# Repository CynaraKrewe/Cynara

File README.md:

A microcontroller and FPGA based, modular prototyping solution covering both hardware and software.

This project was started by Sioux Embedded Systems BV employees in their private time.

The aim of this project is to broaden experience and not only in your own discipline. Members are encouraged to both explore beyond their own discipline(s) and provide guidance to other members were they can. Learning & sharing is what we do. In line of this mindset, everything developed within the project will be made available under terms of a permissive (MIT) license.

Some trivia: 
* [Cynara](https://en.wikipedia.org/wiki/Cynara) is a genus in the sunflower family.
* Addon modules for the Carrier are called Petals.

## Ideas & Goals

#### Target audience

Our target audience is everyone up from the semi-professional hobbyist.

#### Tooling

Goals:
* Keep it simple.
* Keep the complete set of mandatory tooling to a minimum.
* Keep tooling cheap, preferably free.
* Don't reinvent the wheel.

#### Carrier

The Carrier is a complete package of software, HDL, hardware, documentation and partial configuration.

#### Petal

A Petal is a complete package of software, HDL, hardware, documentation and partial configuration.

Goals:
* Keep it simple.
* Keep it cheap.
* Provide a Petal template for jumpstarting.

#### Configuration

Goals:
* Configuration needs to be very intuitive.
* The configuration should understand the restrictions of the microcontroller, FPGA, Carrier and Petal(s).
* A configuration should be validated even before compile-time. Validation during actual designing/writing of the configuration would be nice.

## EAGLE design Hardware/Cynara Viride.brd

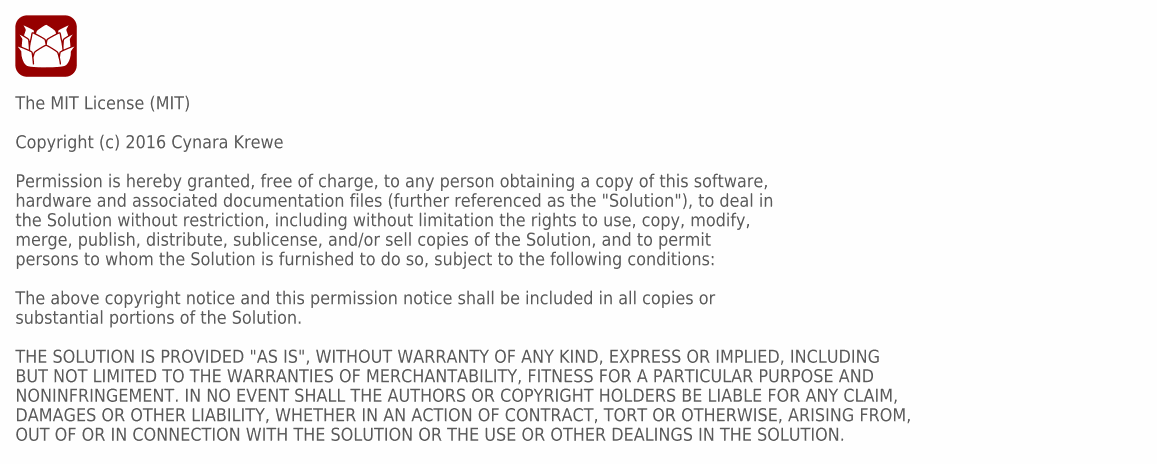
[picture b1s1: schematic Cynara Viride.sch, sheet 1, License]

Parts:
U$21: CYNARA_FRONT; CYNARA_BELOW_W15MM

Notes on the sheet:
The MIT License (MIT) Copyright (c) 2016 Cynara Krewe Permission is hereby granted, free of charge, to any person obtaining a copy of this software, hardware and associated documentation files (further referenced as the "Solution"), to deal in the Solution without restriction, including without lim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

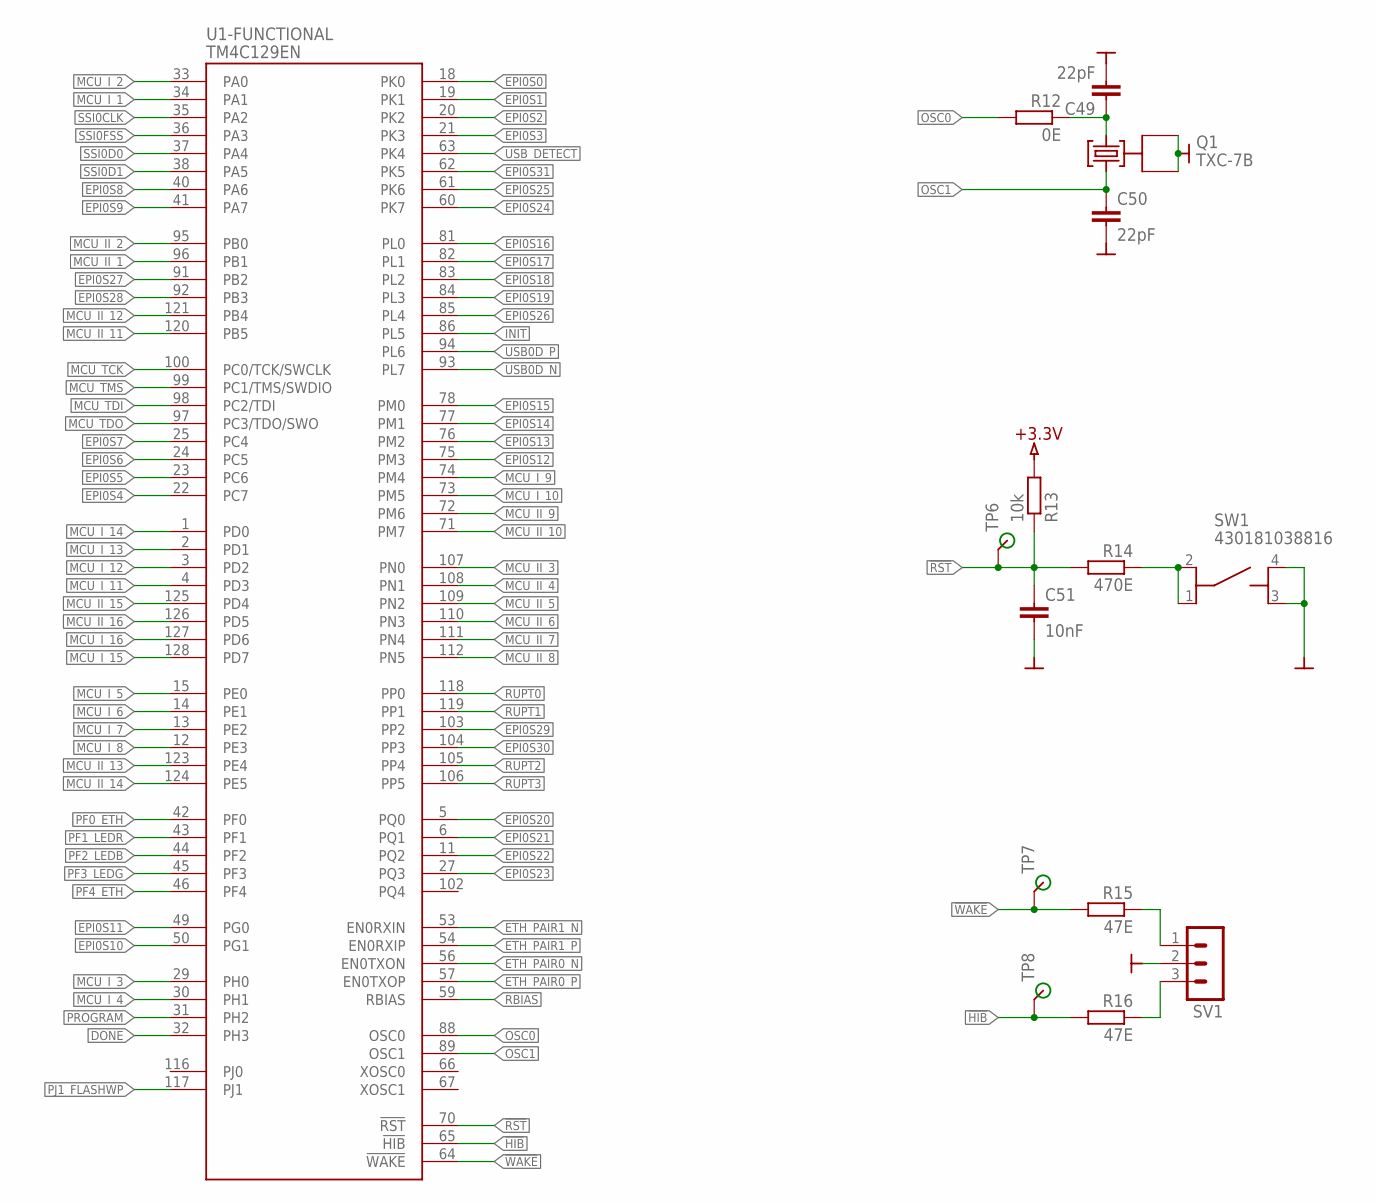
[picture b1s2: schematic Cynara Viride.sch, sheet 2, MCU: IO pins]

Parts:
C49, C50: 22pF; C0603
C51: 10nF; C0603
Q1: TXC-7B
R12: 0E; R0603
R13: 10k; R0603
R14: 470E; R0603
R15, R16: 47E; R0603
SV1: MA03-1
SW1: 430181038816
TP6, TP7, TP8: TP-SMD
U1: TM4C129EN; S-PQFP-G128

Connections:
!HIB: R16.2, TP8.1, U1.65 (!HIB)
!RST: C51.1, R13.1, R14.2, TP6.1, U1.70 (!RST); also elsewhere on the board
!WAKE: R15.2, TP7.1, U1.64 (!WAKE)
+3.3V: R13.2; also elsewhere on the board
DONE: U1.32 (PH3); also elsewhere on the board
EPI0S0: U1.18 (PK0); also elsewhere on the board
EPI0S1: U1.19 (PK1); also elsewhere on the board
EPI0S2: U1.20 (PK2); also elsewhere on the board
EPI0S3: U1.21 (PK3); also elsewhere on the board
EPI0S4: U1.22 (PC7); also elsewhere on the board
EPI0S5: U1.23 (PC6); also elsewhere on the board
EPI0S6: U1.24 (PC5); also elsewhere on the board
EPI0S7: U1.25 (PC4); also elsewhere on the board
EPI0S8: U1.40 (PA6); also elsewhere on the board
EPI0S9: U1.41 (PA7); also elsewhere on the board
EPI0S10: U1.50 (PG1); also elsewhere on the board
EPI0S11: U1.49 (PG0); also elsewhere on the board
EPI0S12: U1.75 (PM3); also elsewhere on the board
EPI0S13: U1.76 (PM2); also elsewhere on the board
EPI0S14: U1.77 (PM1); also elsewhere on the board
EPI0S15: U1.78 (PM0); also elsewhere on the board
EPI0S16: U1.81 (PL0); also elsewhere on the board
EPI0S17: U1.82 (PL1); also elsewhere on the board
EPI0S18: U1.83 (PL2); also elsewhere on the board
EPI0S19: U1.84 (PL3); also elsewhere on the board
EPI0S20: U1.5 (PQ0); also elsewhere on the board
EPI0S21: U1.6 (PQ1); also elsewhere on the board
EPI0S22: U1.11 (PQ2); also elsewhere on the board
EPI0S23: U1.27 (PQ3); also elsewhere on the board
EPI0S24: U1.60 (PK7); also elsewhere on the board
EPI0S25: U1.61 (PK6); also elsewhere on the board
EPI0S26: U1.85 (PL4); also elsewhere on the board
EPI0S27: U1.91 (PB2); also elsewhere on the board
EPI0S28: U1.92 (PB3); also elsewhere on the board
EPI0S29: U1.103 (PP2); also elsewhere on the board
EPI0S30: U1.104 (PP3); also elsewhere on the board
EPI0S31: U1.62 (PK5); also elsewhere on the board
ETH_PAIR0_N: U1.56 (EN0TXON); also elsewhere on the board
ETH_PAIR0_P: U1.57 (EN0TXOP); also elsewhere on the board
ETH_PAIR1_N: U1.53 (EN0RXIN); also elsewhere on the board
ETH_PAIR1_P: U1.54 (EN0RXIP); also elsewhere on the board
GND: C49.2, C50.2, C51.2, Q1.2 (GND), Q1.4 (GND), SV1.2, SW1.3, SW1.4; also elsewhere on the board
INIT: U1.86 (PL5); also elsewhere on the board
MCU_II_1: U1.96 (PB1); also elsewhere on the board
MCU_II_2: U1.95 (PB0); also elsewhere on the board
MCU_II_3: U1.107 (PN0); also elsewhere on the board
MCU_II_4: U1.108 (PN1); also elsewhere on the board
MCU_II_5: U1.109 (PN2); also elsewhere on the board
MCU_II_6: U1.110 (PN3); also elsewhere on the board
MCU_II_7: U1.111 (PN4); also elsewhere on the board
MCU_II_8: U1.112 (PN5); also elsewhere on the board
MCU_II_9: U1.72 (PM6); also elsewhere on the board
MCU_II_10: U1.71 (PM7); also elsewhere on the board
MCU_II_11: U1.120 (PB5); also elsewhere on the board
MCU_II_12: U1.121 (PB4); also elsewhere on the board
MCU_II_13: U1.123 (PE4); also elsewhere on the board
MCU_II_14: U1.124 (PE5); also elsewhere on the board
MCU_II_15: U1.125 (PD4); also elsewhere on the board
MCU_II_16: U1.126 (PD5); also elsewhere on the board
MCU_I_1: U1.34 (PA1); also elsewhere on the board
MCU_I_2: U1.33 (PA0); also elsewhere on the board
MCU_I_3: U1.29 (PH0); also elsewhere on the board
MCU_I_4: U1.30 (PH1); also elsewhere on the board
MCU_I_5: U1.15 (PE0); also elsewhere on the board
MCU_I_6: U1.14 (PE1); also elsewhere on the board
MCU_I_7: U1.13 (PE2); also elsewhere on the board
MCU_I_8: U1.12 (PE3); also elsewhere on the board
MCU_I_9: U1.74 (PM4); also elsewhere on the board
MCU_I_10: U1.73 (PM5); also elsewhere on the board
MCU_I_11: U1.4 (PD3); also elsewhere on the board
MCU_I_12: U1.3 (PD2); also elsewhere on the board
MCU_I_13: U1.2 (PD1); also elsewhere on the board
MCU_I_14: U1.1 (PD0); also elsewhere on the board
MCU_I_15: U1.128 (PD7); also elsewhere on the board
MCU_I_16: U1.127 (PD6); also elsewhere on the board
MCU_TCK: U1.100 (PC0/TCK/SWCLK); also elsewhere on the board
MCU_TDI: U1.98 (PC2/TDI); also elsewhere on the board
MCU_TDO: U1.97 (PC3/TDO/SWO); also elsewhere on the board
MCU_TMS: U1.99 (PC1/TMS/SWDIO); also elsewhere on the board
unnamed: R15.1, SV1.1
unnamed: C49.1, Q1.1 (XTALA), R12.1
unnamed: R14.1, SW1.1, SW1.2
unnamed: R16.1, SV1.3
OSC0: R12.2, U1.88 (OSC0)
OSC1: C50.1, Q1.3 (XTALB), U1.89 (OSC1)
PF0_ETH: U1.42 (PF0); also elsewhere on the board
PF1_LEDR: U1.43 (PF1); also elsewhere on the board
PF2_LEDB: U1.44 (PF2); also elsewhere on the board
PF3_LEDG: U1.45 (PF3); also elsewhere on the board
PF4_ETH: U1.46 (PF4); also elsewhere on the board
PJ1_FLASHWP: U1.117 (PJ1); also elsewhere on the board
PROGRAM: U1.31 (PH2); also elsewhere on the board
RBIAS: U1.59 (RBIAS); also elsewhere on the board
RUPT0: U1.118 (PP0); also elsewhere on the board
RUPT1: U1.119 (PP1); also elsewhere on the board
RUPT2: U1.105 (PP4); also elsewhere on the board
RUPT3: U1.106 (PP5); also elsewhere on the board
SSI0CLK: U1.35 (PA2); also elsewhere on the board
SSI0D0: U1.37 (PA4); also elsewhere on the board
SSI0D1: U1.38 (PA5); also elsewhere on the board
SSI0FSS: U1.36 (PA3); also elsewhere on the board
USB0D_N: U1.93 (PL7); also elsewhere on the board
USB0D_P: U1.94 (PL6); also elsewhere on the board
USB_DETECT: U1.63 (PK4); also elsewhere on the board

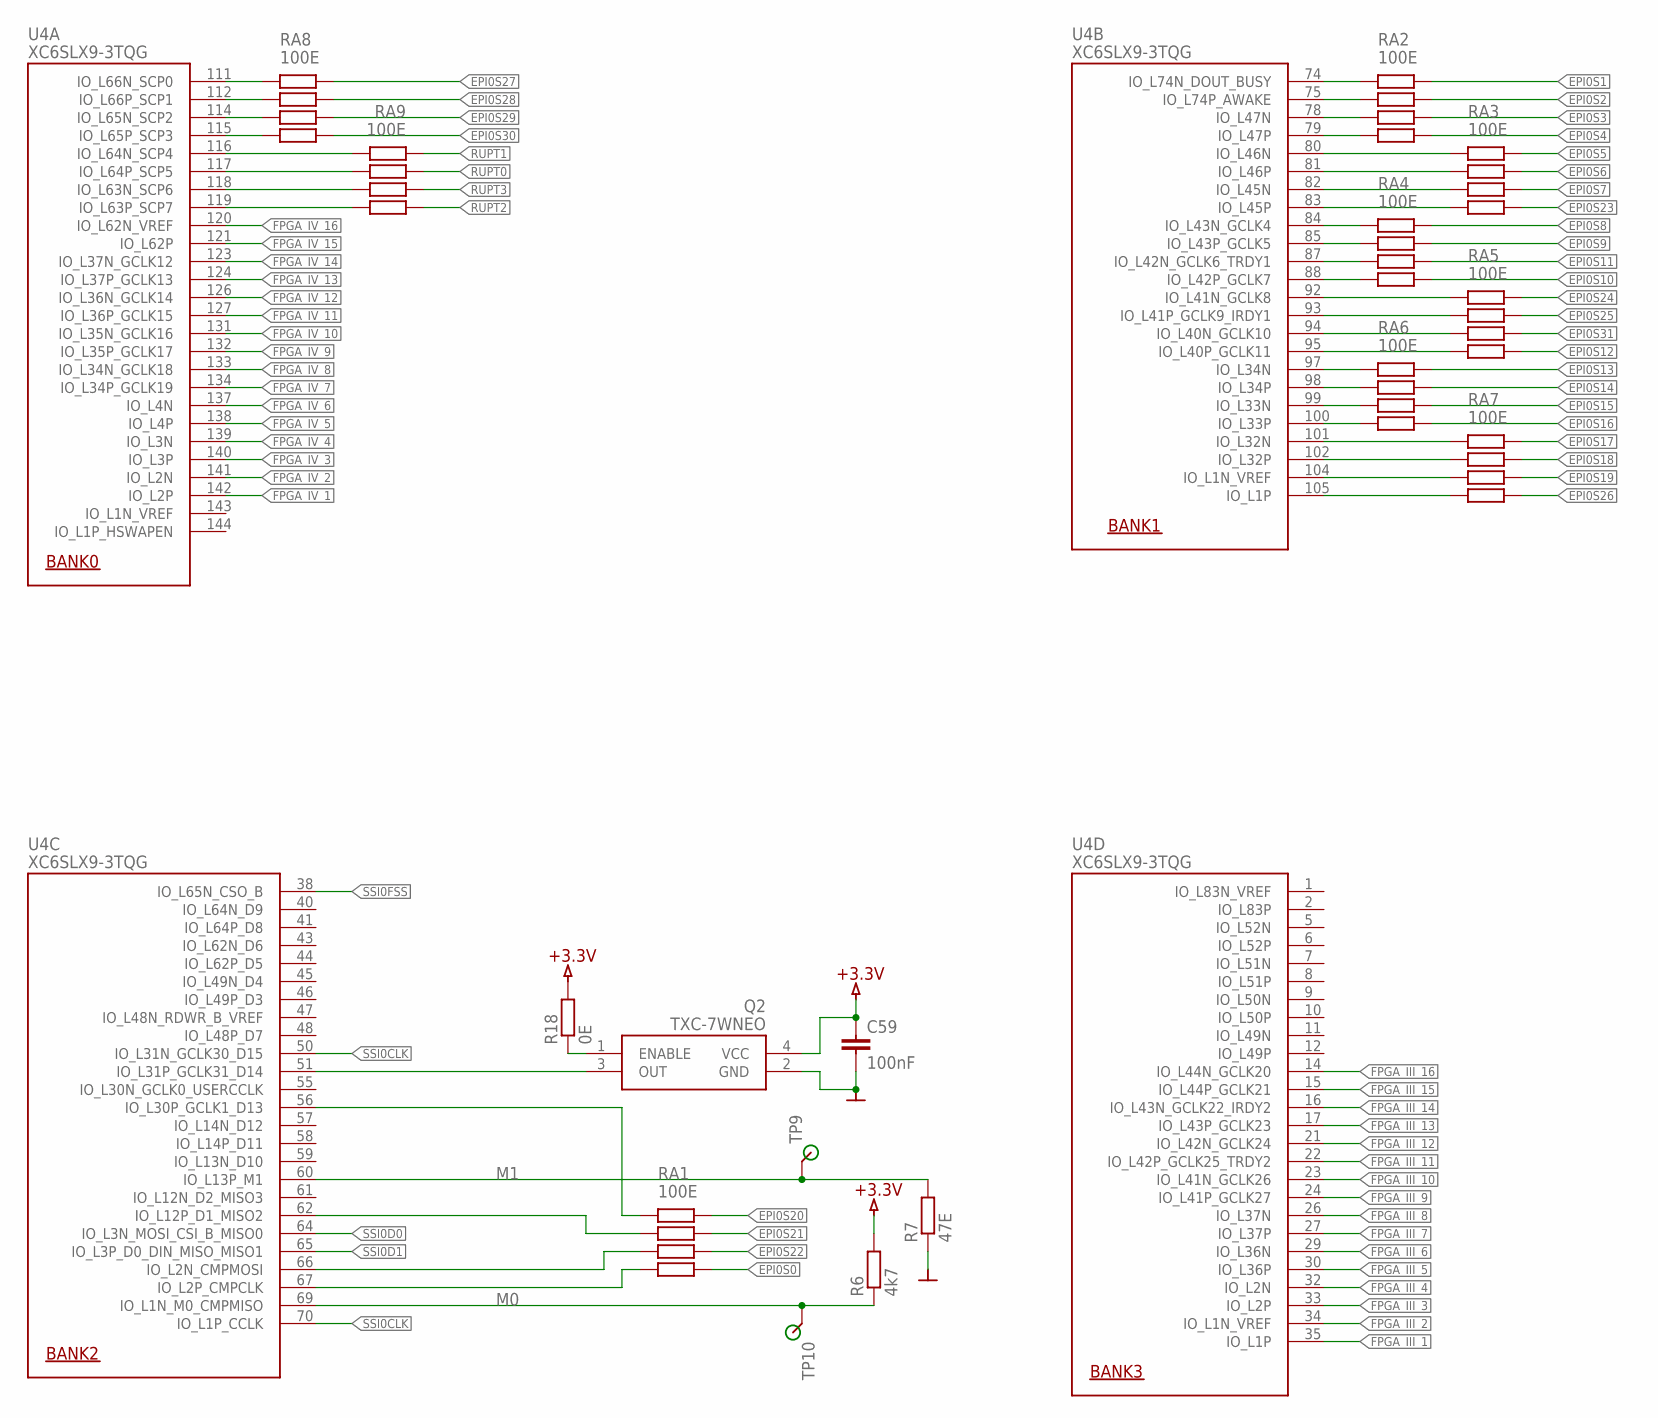
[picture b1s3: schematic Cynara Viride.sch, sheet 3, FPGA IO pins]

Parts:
C59: 100nF; C0603
Q2: TXC-7WNEO; TXC-7W
R6: 4k7; R0603
R7: 47E; R0603
R18: 0E; R0603
RA1, RA2, RA3, RA4, RA5, RA6, RA7, RA8, RA9: 100E; CRA06S
TP9, TP10: TP-SMD
U4: XC6SLX9-3TQG; TQG144

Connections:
+3.3V: C59.1, Q2.4 (VCC), R6.2, R18.2; also elsewhere on the board
EPI0S0: RA1.4B; also elsewhere on the board
EPI0S1: RA2.1B; also elsewhere on the board
EPI0S2: RA2.2B; also elsewhere on the board
EPI0S3: RA2.3B; also elsewhere on the board
EPI0S4: RA2.4B; also elsewhere on the board
EPI0S5: RA3.1B; also elsewhere on the board
EPI0S6: RA3.2B; also elsewhere on the board
EPI0S7: RA3.3B; also elsewhere on the board
EPI0S8: RA4.1B; also elsewhere on the board
EPI0S9: RA4.2B; also elsewhere on the board
EPI0S10: RA4.4B; also elsewhere on the board
EPI0S11: RA4.3B; also elsewhere on the board
EPI0S12: RA5.4B; also elsewhere on the board
EPI0S13: RA6.1B; also elsewhere on the board
EPI0S14: RA6.2B; also elsewhere on the board
EPI0S15: RA6.3B; also elsewhere on the board
EPI0S16: RA6.4B; also elsewhere on the board
EPI0S17: RA7.1B; also elsewhere on the board
EPI0S18: RA7.2B; also elsewhere on the board
EPI0S19: RA7.3B; also elsewhere on the board
EPI0S20: RA1.1B; also elsewhere on the board
EPI0S21: RA1.2B; also elsewhere on the board
EPI0S22: RA1.3B; also elsewhere on the board
EPI0S23: RA3.4B; also elsewhere on the board
EPI0S24: RA5.1B; also elsewhere on the board
EPI0S25: RA5.2B; also elsewhere on the board
EPI0S26: RA7.4B; also elsewhere on the board
EPI0S27: RA8.1B; also elsewhere on the board
EPI0S28: RA8.2B; also elsewhere on the board
EPI0S29: RA8.3B; also elsewhere on the board
EPI0S30: RA8.4B; also elsewhere on the board
EPI0S31: RA5.3B; also elsewhere on the board
FPGA_EPI0S0: RA1.4A, U4.67 (IO_L2P_CMPCLK)
FPGA_EPI0S1: RA2.1A, U4.74 (IO_L74N_DOUT_BUSY)
FPGA_EPI0S2: RA2.2A, U4.75 (IO_L74P_AWAKE)
FPGA_EPI0S3: RA2.3A, U4.78 (IO_L47N)
FPGA_EPI0S4: RA2.4A, U4.79 (IO_L47P)
FPGA_EPI0S5: RA3.1A, U4.80 (IO_L46N)
FPGA_EPI0S6: RA3.2A, U4.81 (IO_L46P)
FPGA_EPI0S7: RA3.3A, U4.82 (IO_L45N)
FPGA_EPI0S8: RA4.1A, U4.84 (IO_L43N_GCLK4)
FPGA_EPI0S9: RA4.2A, U4.85 (IO_L43P_GCLK5)
FPGA_EPI0S10: RA4.4A, U4.88 (IO_L42P_GCLK7)
FPGA_EPI0S11: RA4.3A, U4.87 (IO_L42N_GCLK6_TRDY1)
FPGA_EPI0S12: RA5.4A, U4.95 (IO_L40P_GCLK11)
FPGA_EPI0S13: RA6.1A, U4.97 (IO_L34N)
FPGA_EPI0S14: RA6.2A, U4.98 (IO_L34P)
FPGA_EPI0S15: RA6.3A, U4.99 (IO_L33N)
FPGA_EPI0S16: RA6.4A, U4.100 (IO_L33P)
FPGA_EPI0S17: RA7.1A, U4.101 (IO_L32N)
FPGA_EPI0S18: RA7.2A, U4.102 (IO_L32P)
FPGA_EPI0S19: RA7.3A, U4.104 (IO_L1N_VREF)
FPGA_EPI0S20: RA1.1A, U4.56 (IO_L30P_GCLK1_D13)
FPGA_EPI0S21: RA1.2A, U4.62 (IO_L12P_D1_MISO2)
FPGA_EPI0S22: RA1.3A, U4.66 (IO_L2N_CMPMOSI)
FPGA_EPI0S23: RA3.4A, U4.83 (IO_L45P)
FPGA_EPI0S24: RA5.1A, U4.92 (IO_L41N_GCLK8)
FPGA_EPI0S25: RA5.2A, U4.93 (IO_L41P_GCLK9_IRDY1)
FPGA_EPI0S26: RA7.4A, U4.105 (IO_L1P)
FPGA_EPI0S27: RA8.1A, U4.111 (IO_L66N_SCP0)
FPGA_EPI0S28: RA8.2A, U4.112 (IO_L66P_SCP1)
FPGA_EPI0S29: RA8.3A, U4.114 (IO_L65N_SCP2)
FPGA_EPI0S30: RA8.4A, U4.115 (IO_L65P_SCP3)
FPGA_EPI0S31: RA5.3A, U4.94 (IO_L40N_GCLK10)
FPGA_III_1: U4.35 (IO_L1P); also elsewhere on the board
FPGA_III_2: U4.34 (IO_L1N_VREF); also elsewhere on the board
FPGA_III_3: U4.33 (IO_L2P); also elsewhere on the board
FPGA_III_4: U4.32 (IO_L2N); also elsewhere on the board
FPGA_III_5: U4.30 (IO_L36P); also elsewhere on the board
FPGA_III_6: U4.29 (IO_L36N); also elsewhere on the board
FPGA_III_7: U4.27 (IO_L37P); also elsewhere on the board
FPGA_III_8: U4.26 (IO_L37N); also elsewhere on the board
FPGA_III_9: U4.24 (IO_L41P_GCLK27); also elsewhere on the board
FPGA_III_10: U4.23 (IO_L41N_GCLK26); also elsewhere on the board
FPGA_III_11: U4.22 (IO_L42P_GCLK25_TRDY2); also elsewhere on the board
FPGA_III_12: U4.21 (IO_L42N_GCLK24); also elsewhere on the board
FPGA_III_13: U4.17 (IO_L43P_GCLK23); also elsewhere on the board
FPGA_III_14: U4.16 (IO_L43N_GCLK22_IRDY2); also elsewhere on the board
FPGA_III_15: U4.15 (IO_L44P_GCLK21); also elsewhere on the board
FPGA_III_16: U4.14 (IO_L44N_GCLK20); also elsewhere on the board
FPGA_IV_1: U4.142 (IO_L2P); also elsewhere on the board
FPGA_IV_2: U4.141 (IO_L2N); also elsewhere on the board
FPGA_IV_3: U4.140 (IO_L3P); also elsewhere on the board
FPGA_IV_4: U4.139 (IO_L3N); also elsewhere on the board
FPGA_IV_5: U4.138 (IO_L4P); also elsewhere on the board
FPGA_IV_6: U4.137 (IO_L4N); also elsewhere on the board
FPGA_IV_7: U4.134 (IO_L34P_GCLK19); also elsewhere on the board
FPGA_IV_8: U4.133 (IO_L34N_GCLK18); also elsewhere on the board
FPGA_IV_9: U4.132 (IO_L35P_GCLK17); also elsewhere on the board
FPGA_IV_10: U4.131 (IO_L35N_GCLK16); also elsewhere on the board
FPGA_IV_11: U4.127 (IO_L36P_GCLK15); also elsewhere on the board
FPGA_IV_12: U4.126 (IO_L36N_GCLK14); also elsewhere on the board
FPGA_IV_13: U4.124 (IO_L37P_GCLK13); also elsewhere on the board
FPGA_IV_14: U4.123 (IO_L37N_GCLK12); also elsewhere on the board
FPGA_IV_15: U4.121 (IO_L62P); also elsewhere on the board
FPGA_IV_16: U4.120 (IO_L62N_VREF); also elsewhere on the board
FPGA_OSC: Q2.3 (OUT), U4.51 (IO_L31P_GCLK31_D14)
FPGA_RUPT0: RA9.2B, U4.117 (IO_L64P_SCP5)
FPGA_RUPT1: RA9.1B, U4.116 (IO_L64N_SCP4)
FPGA_RUPT2: RA9.4B, U4.119 (IO_L63P_SCP7)
FPGA_RUPT3: RA9.3B, U4.118 (IO_L63N_SCP6)
GND: C59.2, Q2.2 (GND), R7.1; also elsewhere on the board
M0: R6.1, TP10.1, U4.69 (IO_L1N_M0_CMPMISO)
M1: R7.2, TP9.1, U4.60 (IO_L13P_M1)
unnamed: Q2.1 (ENABLE), R18.1
RUPT0: RA9.2A; also elsewhere on the board
RUPT1: RA9.1A; also elsewhere on the board
RUPT2: RA9.4A; also elsewhere on the board
RUPT3: RA9.3A; also elsewhere on the board
SSI0CLK: U4.50 (IO_L31N_GCLK30_D15), U4.70 (IO_L1P_CCLK); also elsewhere on the board
SSI0D0: U4.64 (IO_L3N_MOSI_CSI_B_MISO0); also elsewhere on the board
SSI0D1: U4.65 (IO_L3P_D0_DIN_MISO_MISO1); also elsewhere on the board
SSI0FSS: U4.38 (IO_L65N_CSO_B); also elsewhere on the board

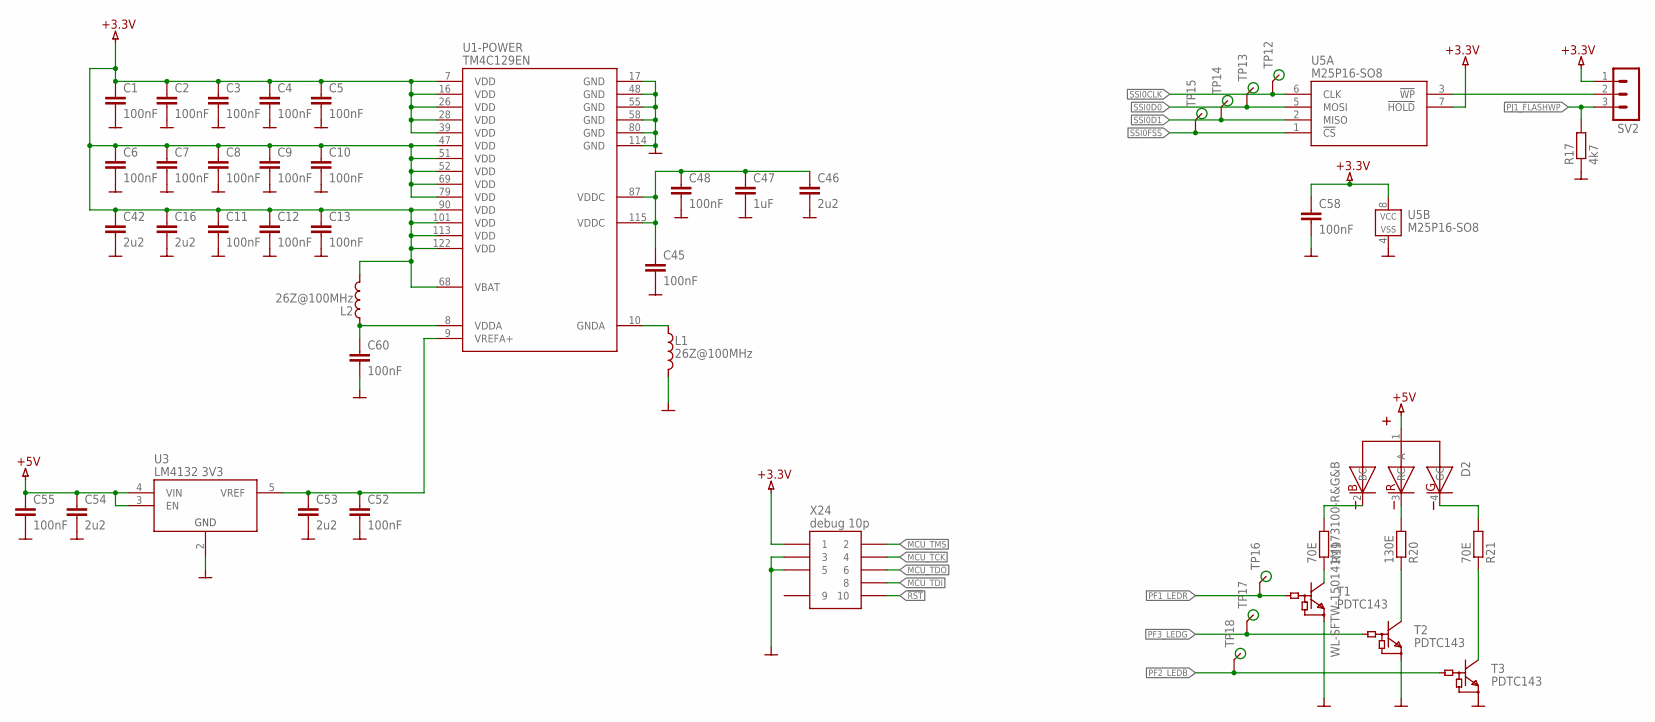
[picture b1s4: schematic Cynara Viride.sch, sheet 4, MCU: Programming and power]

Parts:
C1, C2, C3, C4, C5, C6, C7, C8, C9, C10, C11, C12, C13, C45, C48, C52, C55, C58, C60: 100nF; C0603
C16, C42, C46, C53, C54: 2u2; C0603
C47: 1uF; C0603
D2: WL-SFTW-150141M173100-R&G&B; 3528-COMMON-ANODE
L1, L2: 26Z@100MHz; L1608
R17: 4k7; R0603
R19, R21: 70E; R0603
R20: 130E; R0603
SV2: MA03-1
T1, T2, T3: PDTC143; SOT23-3
TP12, TP13, TP14, TP15, TP16, TP17, TP18: TP-SMD
U1: TM4C129EN; S-PQFP-G128
U3: LM4132 3V3; DBV(R-PDSO-G5)
U5: M25P16-SO8; SOIC127P600X120-8N
X24: debug 10p; DEBUG-CORTEXM10

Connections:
!RST: X24.10; also elsewhere on the board
+3.3V: C1.1, C2.1, C3.1, C4.1, C5.1, C6.1, C7.1, C8.1, C9.1, C10.1, C11.1, C12.1, C13.1, C16.1, C42.1, C58.1, L2.2 (F), SV2.1, U1.7 (VDD), U1.16 (VDD), U1.26 (VDD), U1.28 (VDD), U1.39 (VDD), U1.47 (VDD), U1.51 (VDD), U1.52 (VDD), U1.68 (VBAT), U1.69 (VDD), U1.79 (VDD), U1.90 (VDD), U1.101 (VDD), U1.113 (VDD), U1.122 (VDD), U5.7 (!HOLD), U5.8 (VCC), X24.1; also elsewhere on the board
+5V: C54.1, C55.1, D2.1 (A), U3.3 (EN), U3.4 (VIN); also elsewhere on the board
GND: C1.2, C2.2, C3.2, C4.2, C5.2, C6.2, C7.2, C8.2, C9.2, C10.2, C11.2, C12.2, C13.2, C16.2, C42.2, C45.2, C46.2, C47.2, C48.2, C52.2, C53.2, C54.2, C55.2, C58.2, C60.2, L1.2 (F), R17.1, T1.2 (E), T2.2 (E), T3.2 (E), U1.17 (GND), U1.48 (GND), U1.55 (GND), U1.58 (GND), U1.80 (GND), U1.114 (GND), U3.2 (GND), U5.4 (VSS), X24.3, X24.5; also elsewhere on the board
GNDA: L1.1 (E), U1.10 (GNDA)
MCU_TCK: X24.4; also elsewhere on the board
MCU_TDI: X24.8; also elsewhere on the board
MCU_TDO: X24.6; also elsewhere on the board
MCU_TMS: X24.2; also elsewhere on the board
unnamed: D2.2 (BC), R19.2
unnamed: D2.3 (RC), R20.2
unnamed: D2.4 (GC), R21.2
unnamed: R19.1, T1.3 (C)
unnamed: R20.1, T2.3 (C)
unnamed: R21.1, T3.3 (C)
PF1_LEDR: T1.1 (B), TP16.1; also elsewhere on the board
PF2_LEDB: T3.1 (B), TP18.1; also elsewhere on the board
PF3_LEDG: T2.1 (B), TP17.1; also elsewhere on the board
PJ1X: SV2.2, U5.3 (!WP)
PJ1_FLASHWP: R17.2, SV2.3; also elsewhere on the board
SSI0CLK: TP12.1, U5.6 (CLK); also elsewhere on the board
SSI0D0: TP13.1, U5.5 (MOSI); also elsewhere on the board
SSI0D1: TP14.1, U5.2 (MISO); also elsewhere on the board
SSI0FSS: TP15.1, U5.1 (!CS); also elsewhere on the board
VDDA: C60.1, L2.1 (E), U1.8 (VDDA)
VDDC: C45.1, C46.1, C47.1, C48.1, U1.87 (VDDC), U1.115 (VDDC)
VREFA+: C52.1, C53.1, U1.9 (VREFA+), U3.5 (VREF)

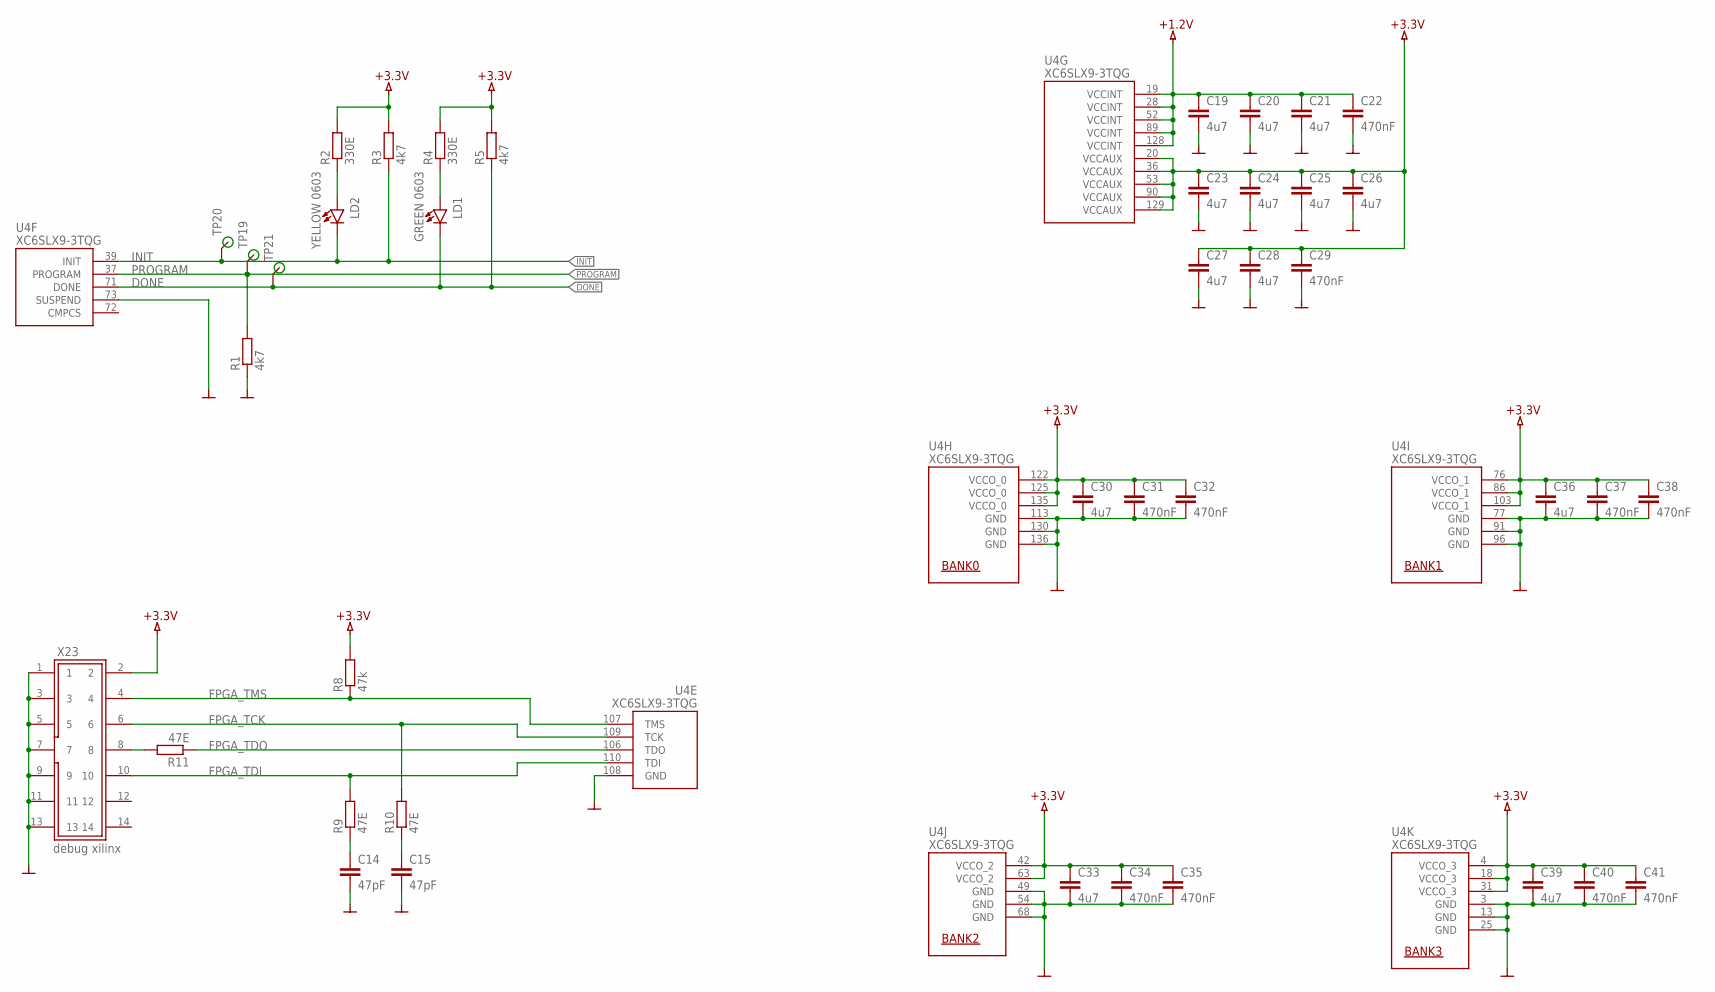
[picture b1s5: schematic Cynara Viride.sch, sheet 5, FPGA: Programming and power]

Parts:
C14, C15: 47pF; C0603
C19, C20, C21, C23, C24, C25, C26, C27, C28, C30, C33, C36, C39: 4u7; C0603
C22, C29, C31, C32, C34, C35, C37, C38, C40, C41: 470nF; C0603
LD1: GREEN 0603; LED_1608
LD2: YELLOW 0603; LED_1608
R1, R3, R5: 4k7; R0603
R2, R4: 330E; R0603
R8: 47k; R0603
R9, R10, R11: 47E; R0603
TP19, TP20, TP21: TP-SMD
U4: XC6SLX9-3TQG; TQG144
X23: debug xilinx; 87832-1420

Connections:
+1.2V: C19.1, C20.1, C21.1, C22.1, U4.19 (VCCINT), U4.28 (VCCINT), U4.52 (VCCINT), U4.89 (VCCINT), U4.128 (VCCINT); also elsewhere on the board
+3.3V: C23.1, C24.1, C25.1, C26.1, C27.1, C28.1, C29.1, C30.1, C31.1, C32.1, C33.1, C34.1, C35.1, C36.1, C37.1, C38.1, C39.1, C40.1, C41.1, R2.2, R3.2, R4.2, R5.2, R8.2, U4.4 (VCCO_3), U4.18 (VCCO_3), U4.20 (VCCAUX), U4.31 (VCCO_3), U4.36 (VCCAUX), U4.42 (VCCO_2), U4.53 (VCCAUX), U4.63 (VCCO_2), U4.76 (VCCO_1), U4.86 (VCCO_1), U4.90 (VCCAUX), U4.103 (VCCO_1), U4.122 (VCCO_0), U4.125 (VCCO_0), U4.129 (VCCAUX), U4.135 (VCCO_0), X23.2; also elsewhere on the board
DONE: LD1.C (K), R5.1, TP21.1, U4.71 (DONE); also elsewhere on the board
FPGA_TCK: R10.2, U4.109 (TCK), X23.6
FPGA_TDI: R9.2, U4.110 (TDI), X23.10
FPGA_TDO: R11.1, U4.106 (TDO)
FPGA_TMS: R8.1, U4.107 (TMS), X23.4
GND: C14.2, C15.2, C19.2, C20.2, C21.2, C22.2, C23.2, C24.2, C25.2, C26.2, C27.2, C28.2, C29.2, C30.2, C31.2, C32.2, C33.2, C34.2, C35.2, C36.2, C37.2, C38.2, C39.2, C40.2, C41.2, R1.1, U4.3 (GND), U4.13 (GND), U4.25 (GND), U4.49 (GND), U4.54 (GND), U4.68 (GND), U4.73 (SUSPEND), U4.77 (GND), U4.91 (GND), U4.96 (GND), U4.108 (GND), U4.113 (GND), U4.130 (GND), U4.136 (GND), X23.1, X23.3, X23.5, X23.7, X23.9, X23.11, X23.13; also elsewhere on the board
INIT: LD2.C (K), R3.1, TP20.1, U4.39 (INIT); also elsewhere on the board
unnamed: LD2.A, R2.1
unnamed: LD1.A, R4.1
unnamed: C14.1, R9.1
unnamed: C15.1, R10.1
unnamed: R11.2, X23.8
PROGRAM: R1.2, TP19.1, U4.37 (PROGRAM); also elsewhere on the board

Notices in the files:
Hardware/Cynara Viride.sch:
CDS: © 2015 Sioux Embedded Systems bv, Eindhoven, The Netherlands
